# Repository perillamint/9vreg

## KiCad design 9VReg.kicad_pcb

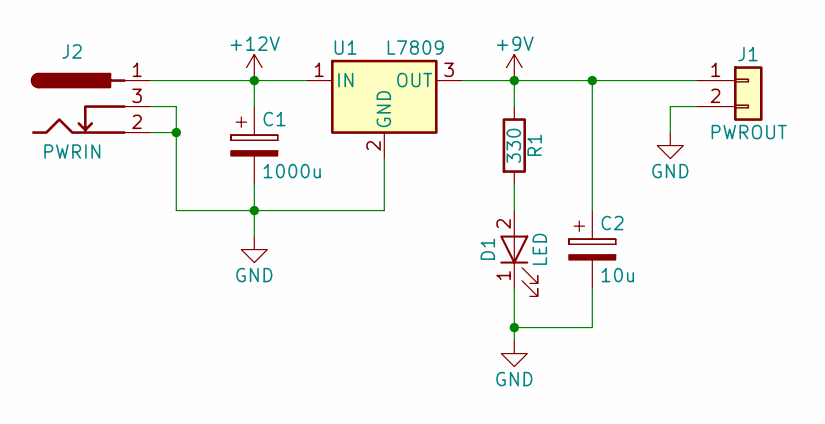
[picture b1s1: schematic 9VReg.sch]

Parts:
C1: 1000u; CP_Radial_D10.0mm_P5.00mm
C2: 10u; CP_Radial_D5.0mm_P2.50mm
D1: LED; LED_D3.0mm
J1: PWROUT; TerminalBlock_Phoenix_MKDS1.5-2pol
J2: PWRIN; BARREL_JACK
R1: 330; R_Axial_DIN0207_L6.3mm_D2.5mm_P10.16mm_Horizontal
U1: L7809; TO-220-3_Vertical

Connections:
+9V: C2.1, J1.1, R1.1, U1.3 (OUT)
+12V: C1.1, J2.1, U1.1 (IN)
GND: C1.2, C2.2, D1.1 (K), J1.2, J2.2, J2.3, U1.2 (GND)
unnamed: D1.2 (A), R1.2

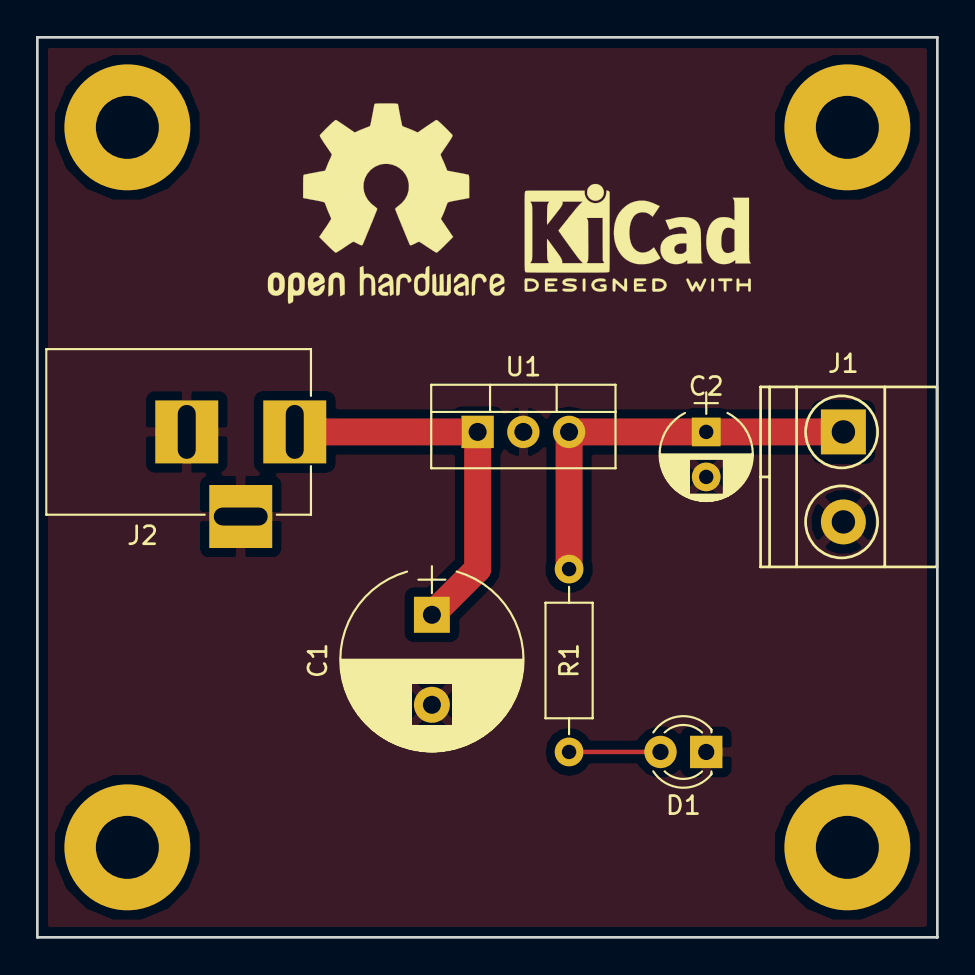
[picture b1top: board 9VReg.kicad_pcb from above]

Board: 2 copper layers, 50.0 x 50.0 mm, 7 parts (0 on the bottom side), 4 nets.

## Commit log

2018-10-10 9VReg Mk. II
